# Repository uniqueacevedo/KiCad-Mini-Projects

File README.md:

# 🧠 KiCad Mini Projects

This folder documents a series of small, self-directed hardware design projects created as part of my ongoing learning in **PCB design, circuit analysis, and embedded systems development**. Each project focuses on practicing a specific concept or workflow step — from schematic capture and component selection to layout, routing, and validation — all using **KiCad**.

These mini builds are my way of exploring the full hardware pipeline hands-on:
- Translating ideas into functional circuit schematics  
- Designing clean, manufacturable two-layer PCBs  
- Reviewing footprints, clearances, and signal paths  
- Experimenting with analog and digital interfaces  
- Bringing each design to life through simulation or prototyping  

While each board is small in scope, the goal is consistency and growth — improving attention to detail, mastering KiCad’s toolset, and strengthening practical intuition for real-world hardware design.  

More projects will be added as I continue refining both **technical skill** and **design discipline** through iteration.

---

*Tools:* KiCad • LTspice • Arduino IDE • Python  
*Focus Areas:* PCB layout • Circuit design • Embedded hardware • Schematic-to-prototype workflow

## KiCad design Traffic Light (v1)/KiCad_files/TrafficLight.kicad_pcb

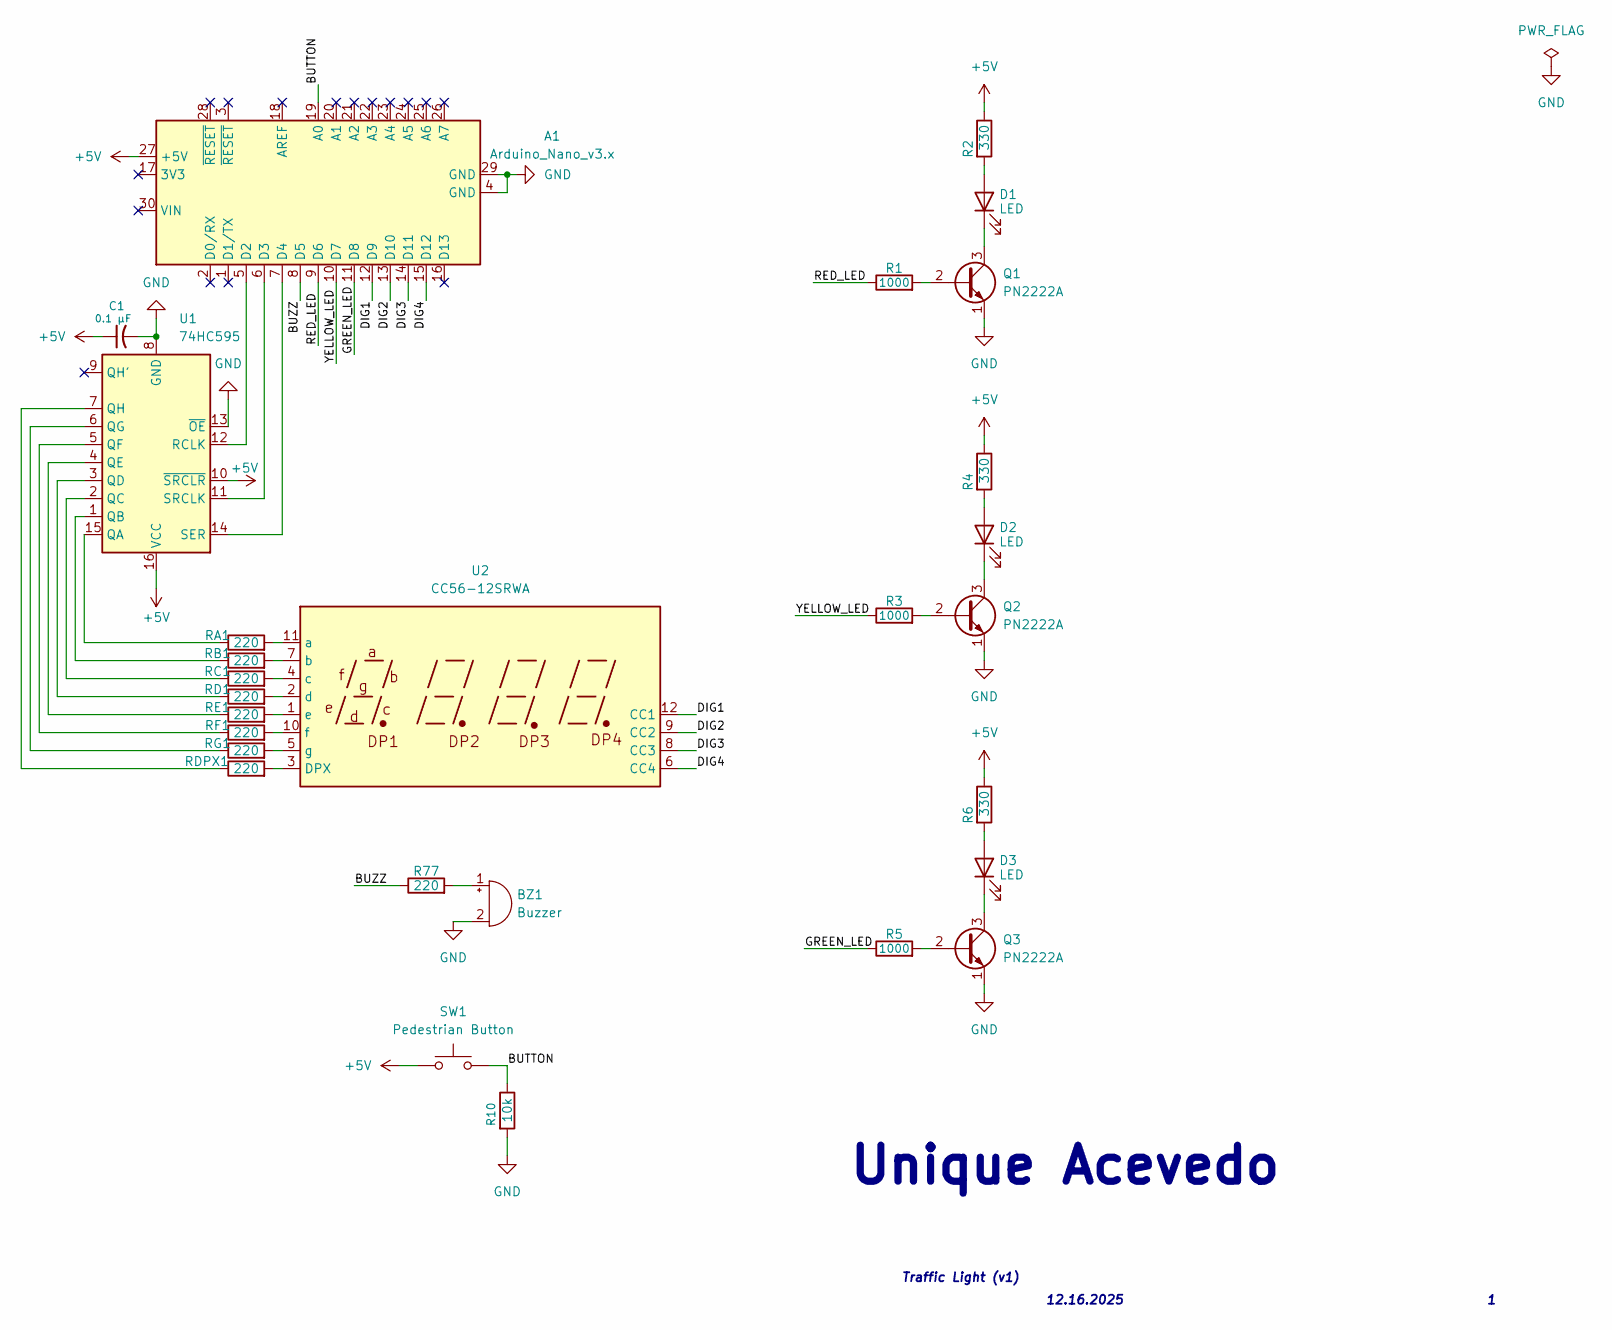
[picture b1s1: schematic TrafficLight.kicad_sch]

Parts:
A1: Arduino_Nano_v3.x; Arduino_Nano_WithMountingHoles
BZ1: Buzzer; Buzzer_12x9.5RM7.6
C1: 0.1 µF; C_Disc_D5.0mm_W2.5mm_P2.50mm
D1, D2, D3: LED; LED_D5.0mm
Q1, Q2, Q3: PN2222A; TO-92_Inline
R1, R3, R5: 1000; R_Axial_DIN0207_L6.3mm_D2.5mm_P10.16mm_Horizontal
R2, R4, R6: 330; R_Axial_DIN0207_L6.3mm_D2.5mm_P10.16mm_Horizontal
R10: 10k; R_Axial_DIN0207_L6.3mm_D2.5mm_P10.16mm_Horizontal
R77: 220; R_Axial_DIN0207_L6.3mm_D2.5mm_P10.16mm_Horizontal
RA1: 220; R_Axial_DIN0207_L6.3mm_D2.5mm_P10.16mm_Horizontal
RB1: 220; R_Axial_DIN0207_L6.3mm_D2.5mm_P10.16mm_Horizontal
RC1: 220; R_Axial_DIN0207_L6.3mm_D2.5mm_P10.16mm_Horizontal
RD1: 220; R_Axial_DIN0207_L6.3mm_D2.5mm_P10.16mm_Horizontal
RDPX1: 220; R_Axial_DIN0207_L6.3mm_D2.5mm_P10.16mm_Horizontal
RE1: 220; R_Axial_DIN0207_L6.3mm_D2.5mm_P10.16mm_Horizontal
RF1: 220; R_Axial_DIN0207_L6.3mm_D2.5mm_P10.16mm_Horizontal
RG1: 220; R_Axial_DIN0207_L6.3mm_D2.5mm_P10.16mm_Horizontal
SW1: Pedestrian Button; SW_PUSH_6mm_H5mm
U1: 74HC595; DIP-16_W7.62mm
U2: CC56-12SRWA; CA56-12SRWA

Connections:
+5V: A1.27 (+5V), C1.1, R2.1, R4.1, R6.1, SW1.1, U1.10 (~SRCLR), U1.16 (VCC)
/BUTTON: A1.19 (A0), R10.1, SW1.2
/BUZZ: A1.8 (D5), R77.1
/DIG1: A1.12 (D9), U2.12 (CC1)
/DIG2: A1.13 (D10), U2.9 (CC2)
/DIG3: A1.14 (D11), U2.8 (CC3)
/DIG4: A1.15 (D12), U2.6 (CC4)
/GREEN_LED: A1.11 (D8), R5.1
/RED_LED: A1.9 (D6), R1.1
/YELLOW_LED: A1.10 (D7), R3.1
GND: A1.4 (GND), A1.29 (GND), BZ1.2 (-), C1.2, Q1.1 (E), Q2.1 (E), Q3.1 (E), R10.2, U1.8 (GND), U1.13 (~OE)
unnamed: A1.5 (D2), U1.12 (RCLK)
unnamed: A1.6 (D3), U1.11 (SRCLK)
unnamed: A1.7 (D4), U1.14 (SER)
unnamed: BZ1.1 (+), R77.2
unnamed: D1.2 (A), R2.2
unnamed: D1.1 (K), Q1.3 (C)
unnamed: D2.2 (A), R4.2
unnamed: D2.1 (K), Q2.3 (C)
unnamed: D3.2 (A), R6.2
unnamed: D3.1 (K), Q3.3 (C)
unnamed: Q1.2 (B), R1.2
unnamed: Q2.2 (B), R3.2
unnamed: Q3.2 (B), R5.2
unnamed: RA1.1, U1.15 (QA)
unnamed: RB1.1, U1.1 (QB)
unnamed: RC1.1, U1.2 (QC)
unnamed: RD1.1, U1.3 (QD)
unnamed: RE1.1, U1.4 (QE)
unnamed: RF1.1, U1.5 (QF)
unnamed: RG1.1, U1.6 (QG)
unnamed: RDPX1.1, U1.7 (QH)
unnamed: RDPX1.2, U2.3 (DPX)
unnamed: RA1.2, U2.11 (a)
unnamed: RB1.2, U2.7 (b)
unnamed: RC1.2, U2.4 (c)
unnamed: RD1.2, U2.2 (d)
unnamed: RE1.2, U2.1 (e)
unnamed: RF1.2, U2.10 (f)
unnamed: RG1.2, U2.5 (g)

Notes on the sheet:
Traffic Light (v1)
Unique Acevedo
12.16.2025

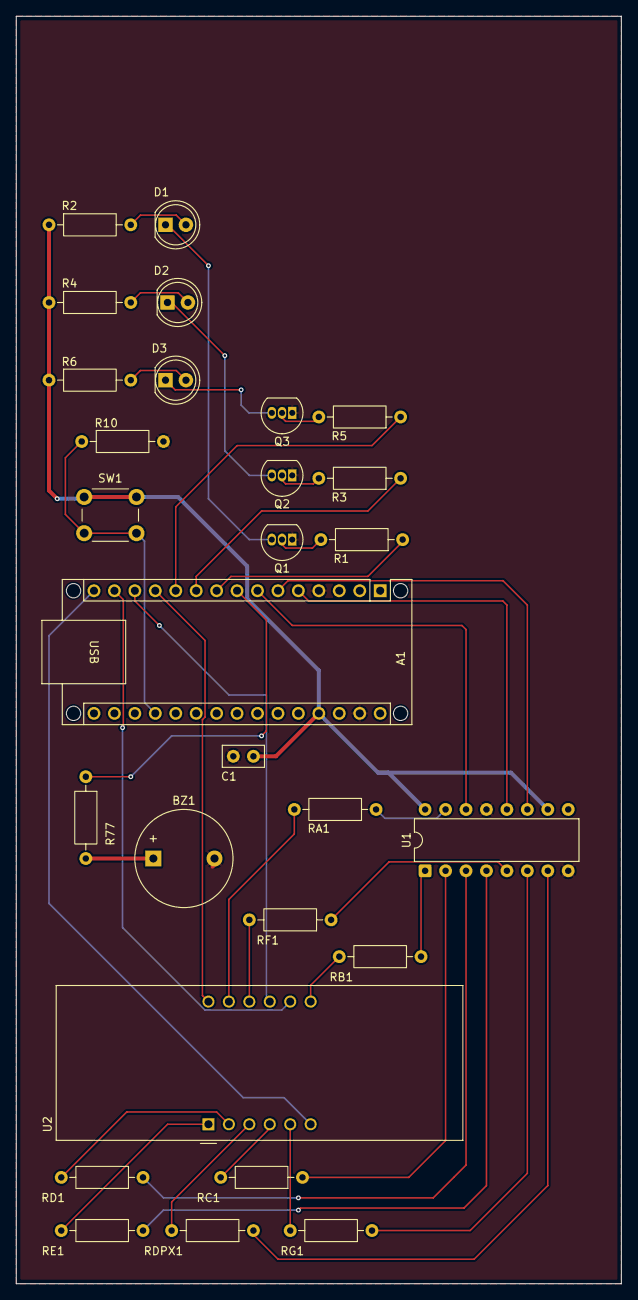
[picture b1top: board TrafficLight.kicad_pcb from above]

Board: 2 copper layers, 75.2 x 157.5 mm, 28 parts (0 on the bottom side), 40 nets.

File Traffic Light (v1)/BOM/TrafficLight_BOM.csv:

"Reference","Qty","Value","DNP","Exclude from BOM","Exclude from Board","Footprint","Datasheet"
"A1","1","Arduino_Nano_v3.x","","","","Module:Arduino_Nano_WithMountingHoles","http://www.mouser.com/pdfdocs/Gravitech_Arduino_Nano3_0.pdf"
"BZ1","1","Buzzer","","","","Buzzer_Beeper:Buzzer_12x9.5RM7.6","~"
"C1","1","0.1 µF","","","","Capacitor_THT:C_Disc_D5.0mm_W2.5mm_P2.50mm",""
"D1,D2,D3","3","LED","","","","LED_THT:LED_D5.0mm","~"
"Q1,Q2,Q3","3","PN2222A","","","","Package_TO_SOT_THT:TO-92_Inline","https://www.onsemi.com/pub/Collateral/PN2222-D.PDF"
"R1,R3,R5","3","1000","","","","Resistor_THT:R_Axial_DIN0207_L6.3mm_D2.5mm_P10.16mm_Horizontal","~"
"R2,R4,R6","3","330","","","","Resistor_THT:R_Axial_DIN0207_L6.3mm_D2.5mm_P10.16mm_Horizontal","~"
"R10","1","10k","","","","Resistor_THT:R_Axial_DIN0207_L6.3mm_D2.5mm_P10.16mm_Horizontal","~"
"R77,RA1,RB1,RC1,RD1,RDPX1,RE1,RF1,RG1","9","220","","","","Resistor_THT:R_Axial_DIN0207_L6.3mm_D2.5mm_P10.16mm_Horizontal","~"
"SW1","1","Pedestrian Button","","","","Button_Switch_THT:SW_PUSH_6mm_H5mm","~"
"U1","1","74HC595","","","","Package_DIP:DIP-16_W7.62mm","http://www.ti.com/lit/ds/symlink/sn74hc595.pdf"
"U2","1","CC56-12SRWA","","","","Display_7Segment:CA56-12SRWA","http://www.kingbrightusa.com/images/catalog/SPEC/CC56-12SRWA.pdf"

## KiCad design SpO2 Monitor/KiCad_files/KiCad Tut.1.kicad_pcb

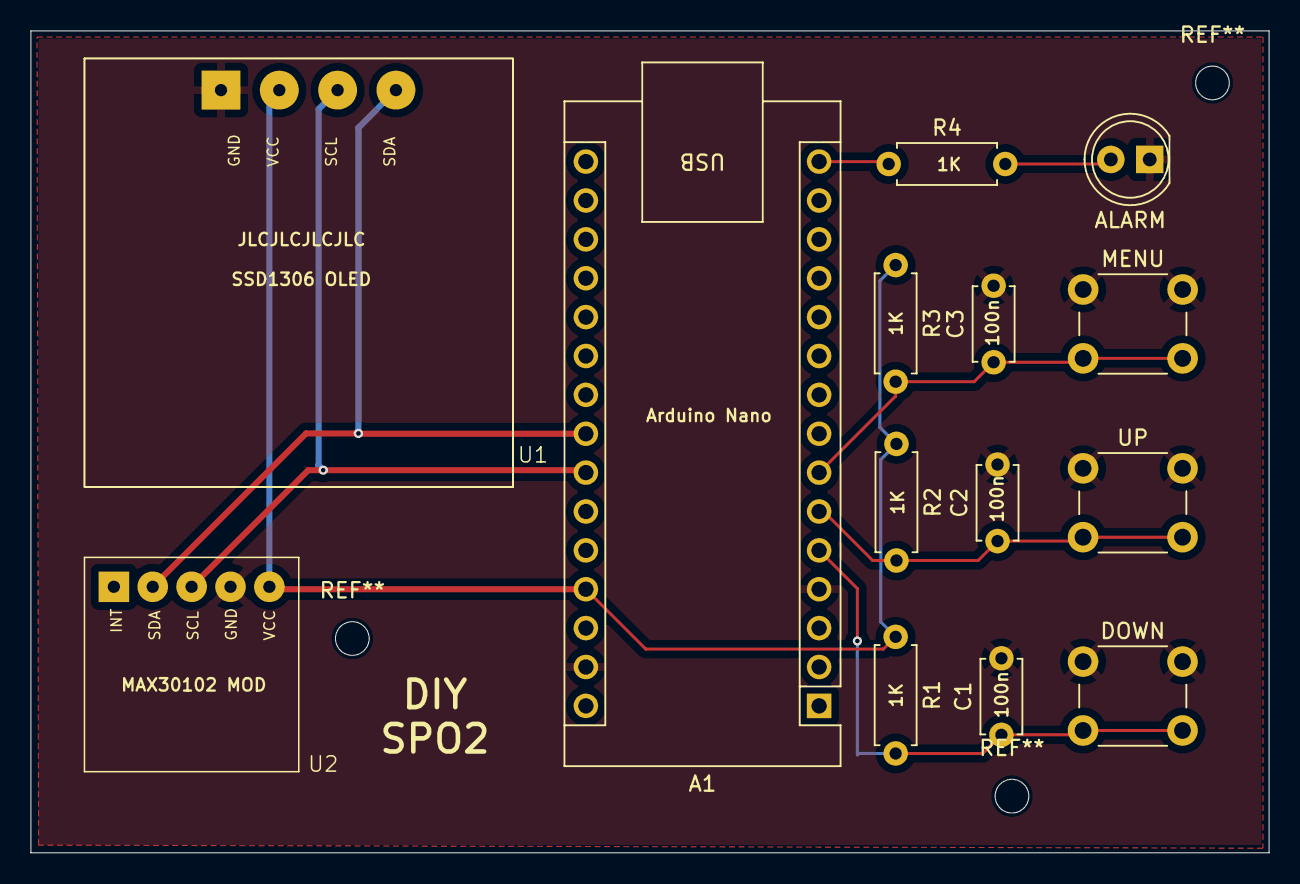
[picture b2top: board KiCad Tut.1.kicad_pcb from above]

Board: 4 copper layers, 80.9 x 53.7 mm, 14 parts (0 on the bottom side), 9 nets.

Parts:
A1: Arduino_Nano_v3.x; Arduino_Nano
ALARM: LED; LED_D5.0mm
C1, C2, C3: 100n; C_Disc_D4.7mm_W2.5mm_P5.00mm
DOWN: SW_Push; SW_PUSH_6mm
MENU: SW_Push; SW_PUSH_6mm
R1, R2, R3, R4: 1k; R_Axial_DIN0207_L6.3mm_D2.5mm_P7.62mm_Horizontal
U1: SSD1306
U2: MAX30102; MAX30102 Module
UP: SW_Push; SW_PUSH_6mm

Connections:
+5V: A1.27 (+5V), R1.1, R2.1, R3.1, U1.2 (VCC), U2.5 (VCC)
GND: A1.4 (GND), A1.29 (GND), ALARM.1 (K), C1.2, C2.2, C3.2, DOWN.1, MENU.1, U1.1 (GND), U2.4 (GND), UP.1
unnamed: A1.23 (A4), U1.4 (SDA), U2.2 (SDA)
unnamed: A1.24 (A5), U1.3 (SCL), U2.3 (SCL)
unnamed: A1.5 (D2), C1.1, DOWN.2, R1.2
unnamed: A1.6 (D3), C2.1, R2.2, UP.2
unnamed: A1.7 (D4), C3.1, MENU.2, R3.2
unnamed: A1.15 (D12), R4.1
unnamed: ALARM.2 (A), R4.2

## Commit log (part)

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2025-09-25 Create BOM
2025-10-12 Update copyright in LICENSE file
2025-10-12 Add project description for SpO₂ Monitor
    Document the design and features of the SpO₂ Monitor project, including schematic, layout, and skills demonstrated.
2025-10-12 Enhance DESC.md with schematic and layout details
    Updated the DESC.md file to include schematic, PCB layout, and 3D render sections with images.
2025-10-12 Remove notes section from DESC.md
    Removed notes section detailing design emphasis and workflow.
2025-10-31 Enhance README with project descriptions and tools
    Expanded the README to include project details and focus areas.
2025-12-17 Create LICENSE
